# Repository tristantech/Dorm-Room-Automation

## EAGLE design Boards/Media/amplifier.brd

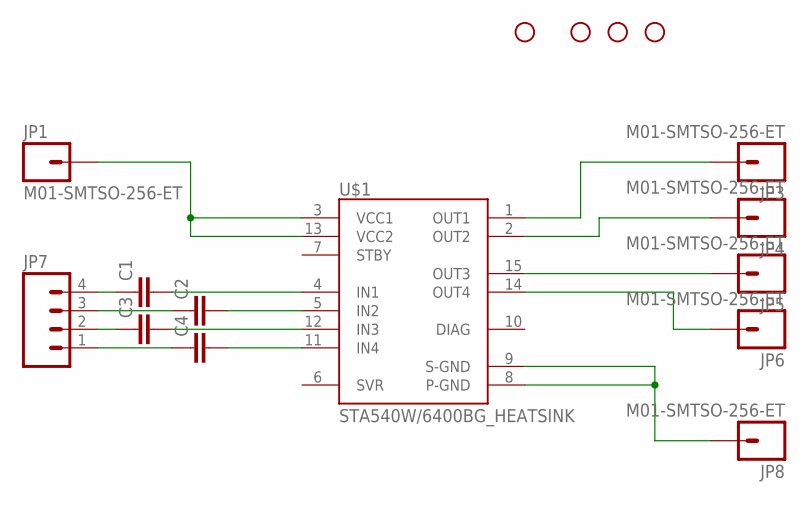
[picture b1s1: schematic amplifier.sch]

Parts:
C1, C2, C3, C4: CAP1206; 1206
JP1, JP3, JP4, JP5, JP6, JP8: M01-SMTSO-256-ET; SMTSO-256-ET
JP7: M04PTH; 1X04
STANDOFF1, STANDOFF2, STANDOFF3, STANDOFF4: STAND-OFF
U$1: STA540W/6400BG_HEATSINK; MULTIWATT15_6400BGHEATSINK

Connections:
unnamed: JP3.P$1, U$1.1 (OUT1)
unnamed: JP4.P$1, U$1.2 (OUT2)
unnamed: JP5.P$1, U$1.15 (OUT3)
unnamed: JP6.P$1, U$1.14 (OUT4)
unnamed: JP8.P$1, U$1.8 (P-GND), U$1.9 (S-GND)
unnamed: JP1.P$1, U$1.3 (VCC1), U$1.13 (VCC2)
unnamed: C4.2, U$1.11 (IN4)
unnamed: C3.2, U$1.12 (IN3)
unnamed: C2.2, U$1.5 (IN2)
unnamed: C1.2, U$1.4 (IN1)
unnamed: C1.1, JP7.4
unnamed: C2.1, JP7.3
unnamed: C3.1, JP7.2
unnamed: C4.1, JP7.1

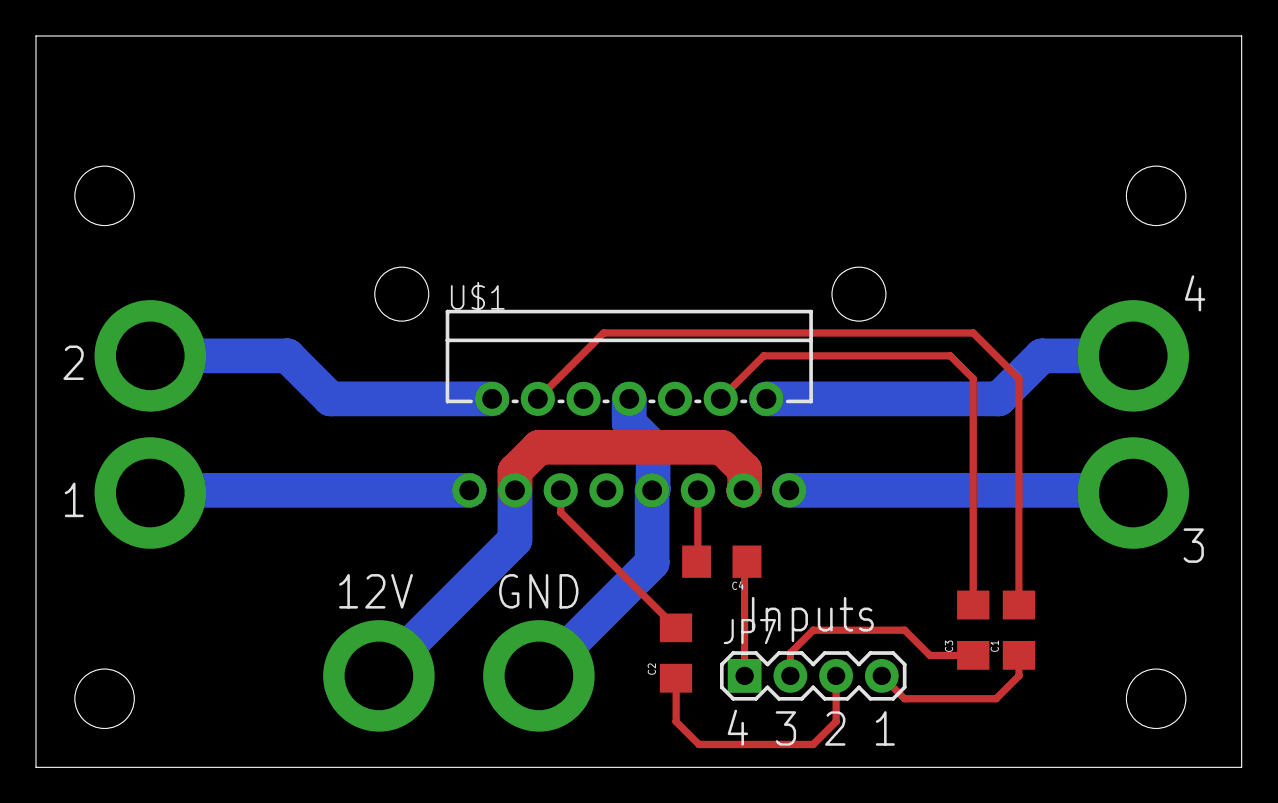
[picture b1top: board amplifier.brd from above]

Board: 2 copper layers, 67.0 x 40.6 mm, 16 parts (0 on the bottom side), 14 nets.

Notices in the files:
parts and their libraries:
1_SparkFun-Connectors: Licensing: CC v3.0 Share-Alike You are welcome to use this library for commercial purposes.
